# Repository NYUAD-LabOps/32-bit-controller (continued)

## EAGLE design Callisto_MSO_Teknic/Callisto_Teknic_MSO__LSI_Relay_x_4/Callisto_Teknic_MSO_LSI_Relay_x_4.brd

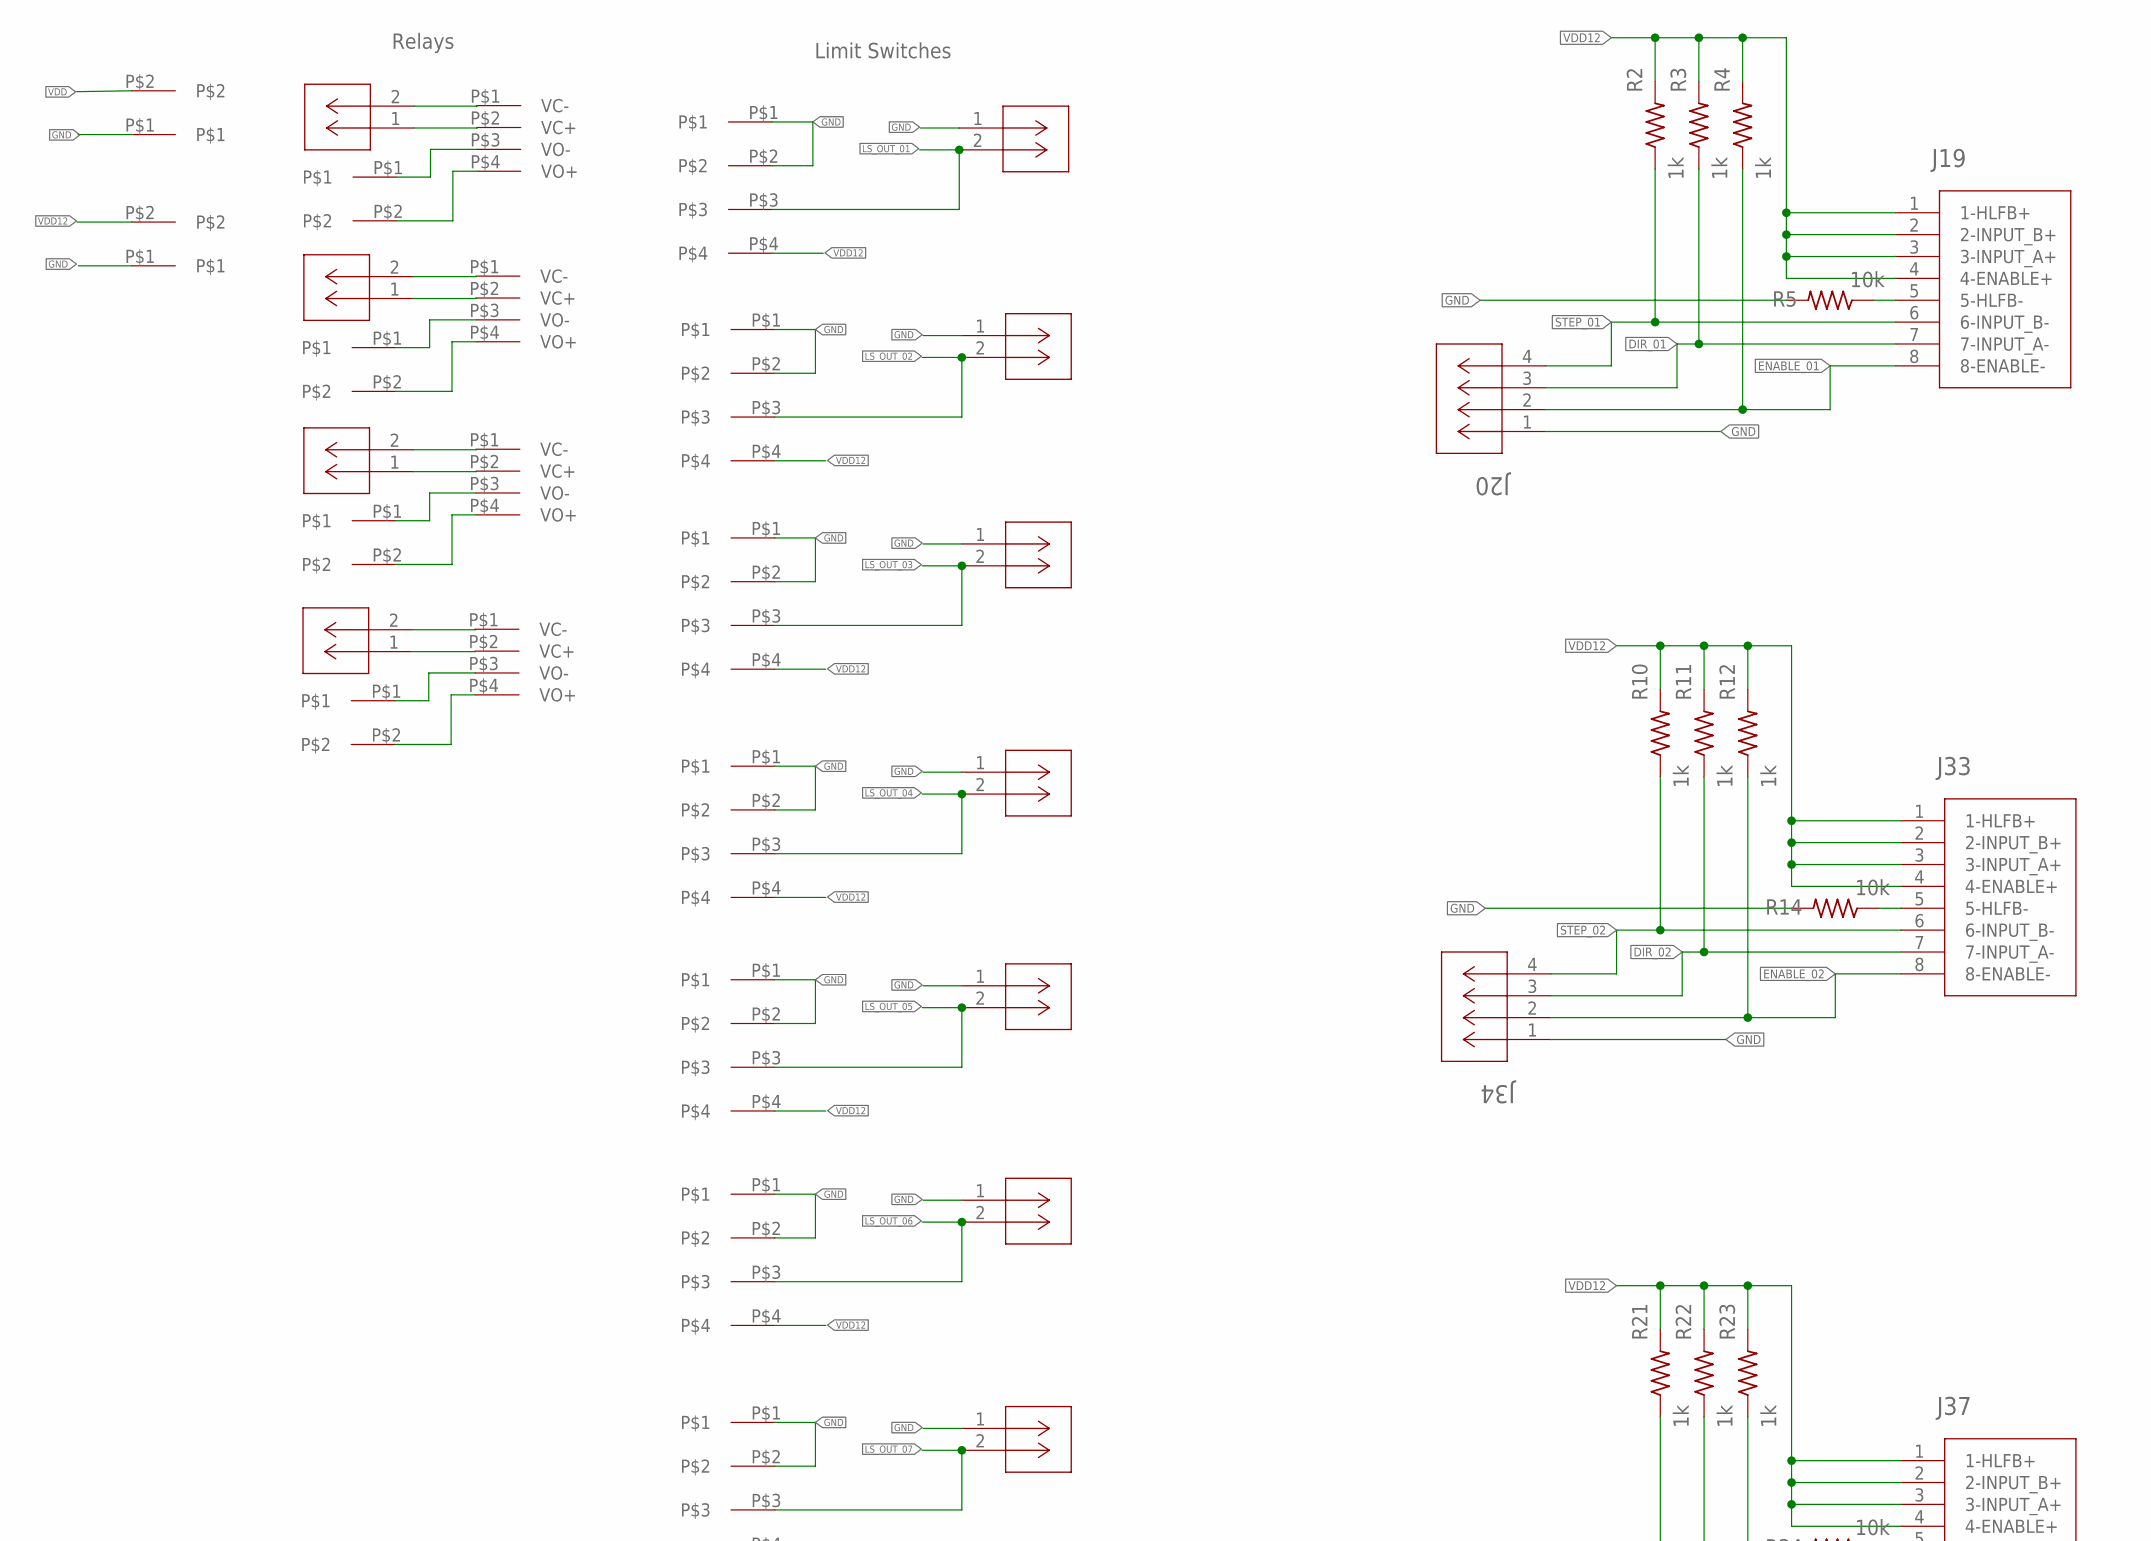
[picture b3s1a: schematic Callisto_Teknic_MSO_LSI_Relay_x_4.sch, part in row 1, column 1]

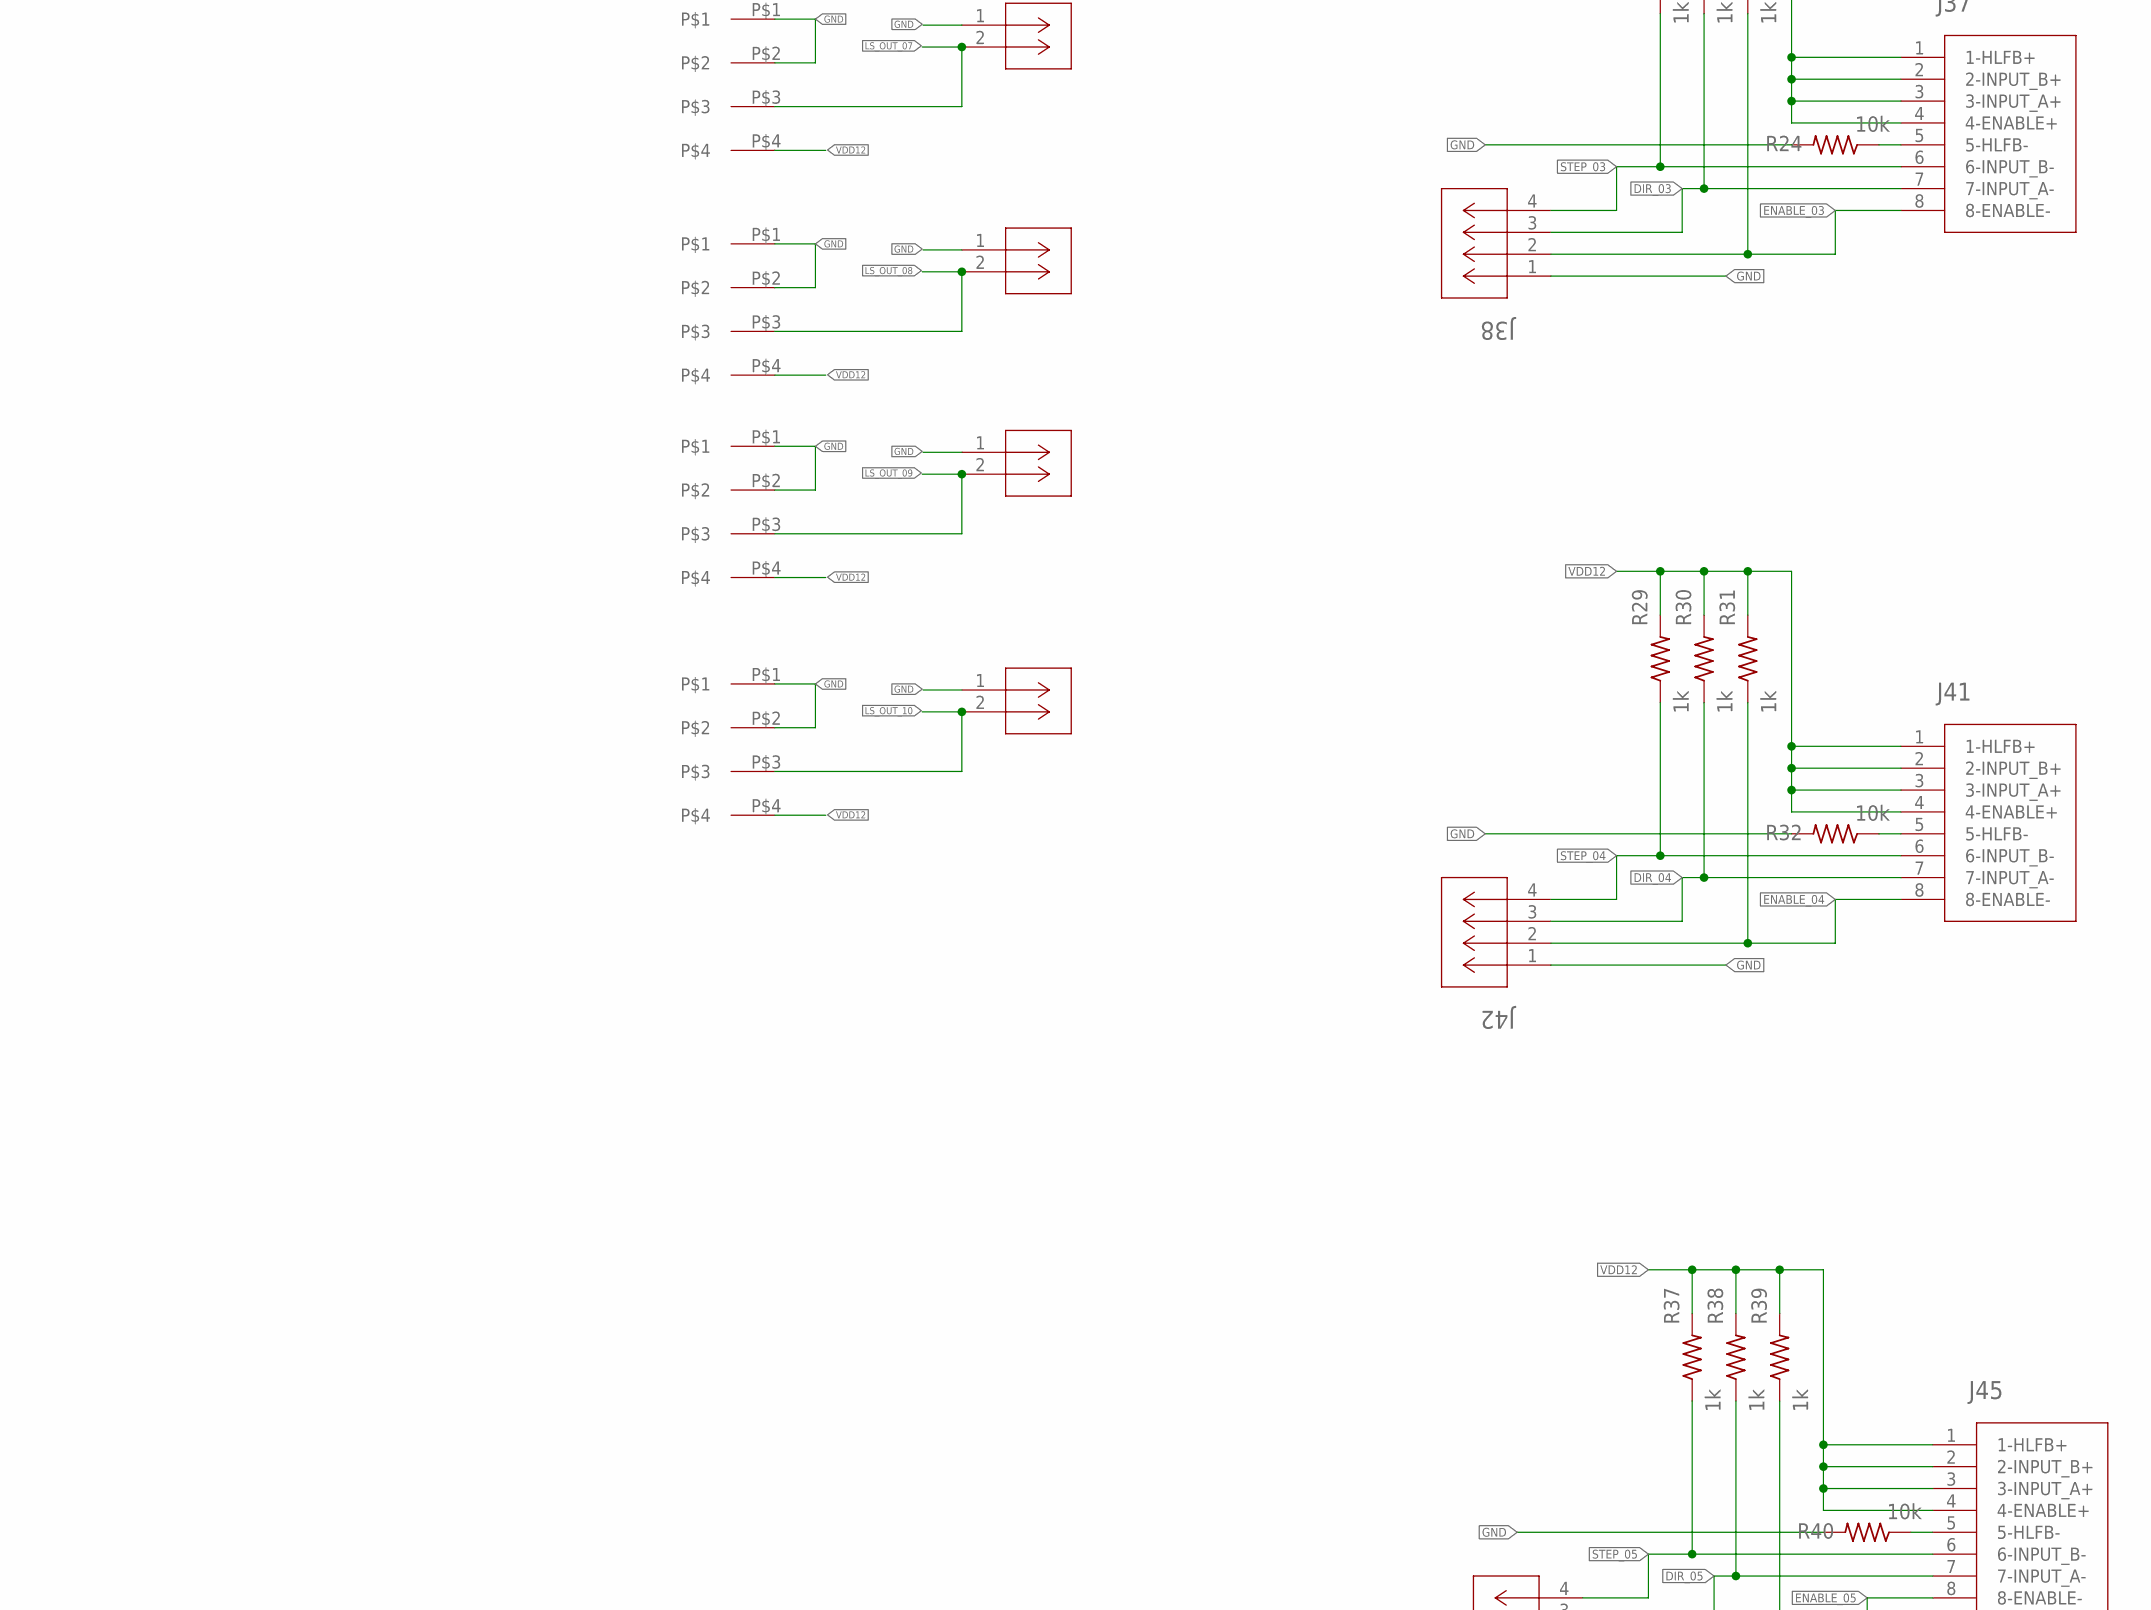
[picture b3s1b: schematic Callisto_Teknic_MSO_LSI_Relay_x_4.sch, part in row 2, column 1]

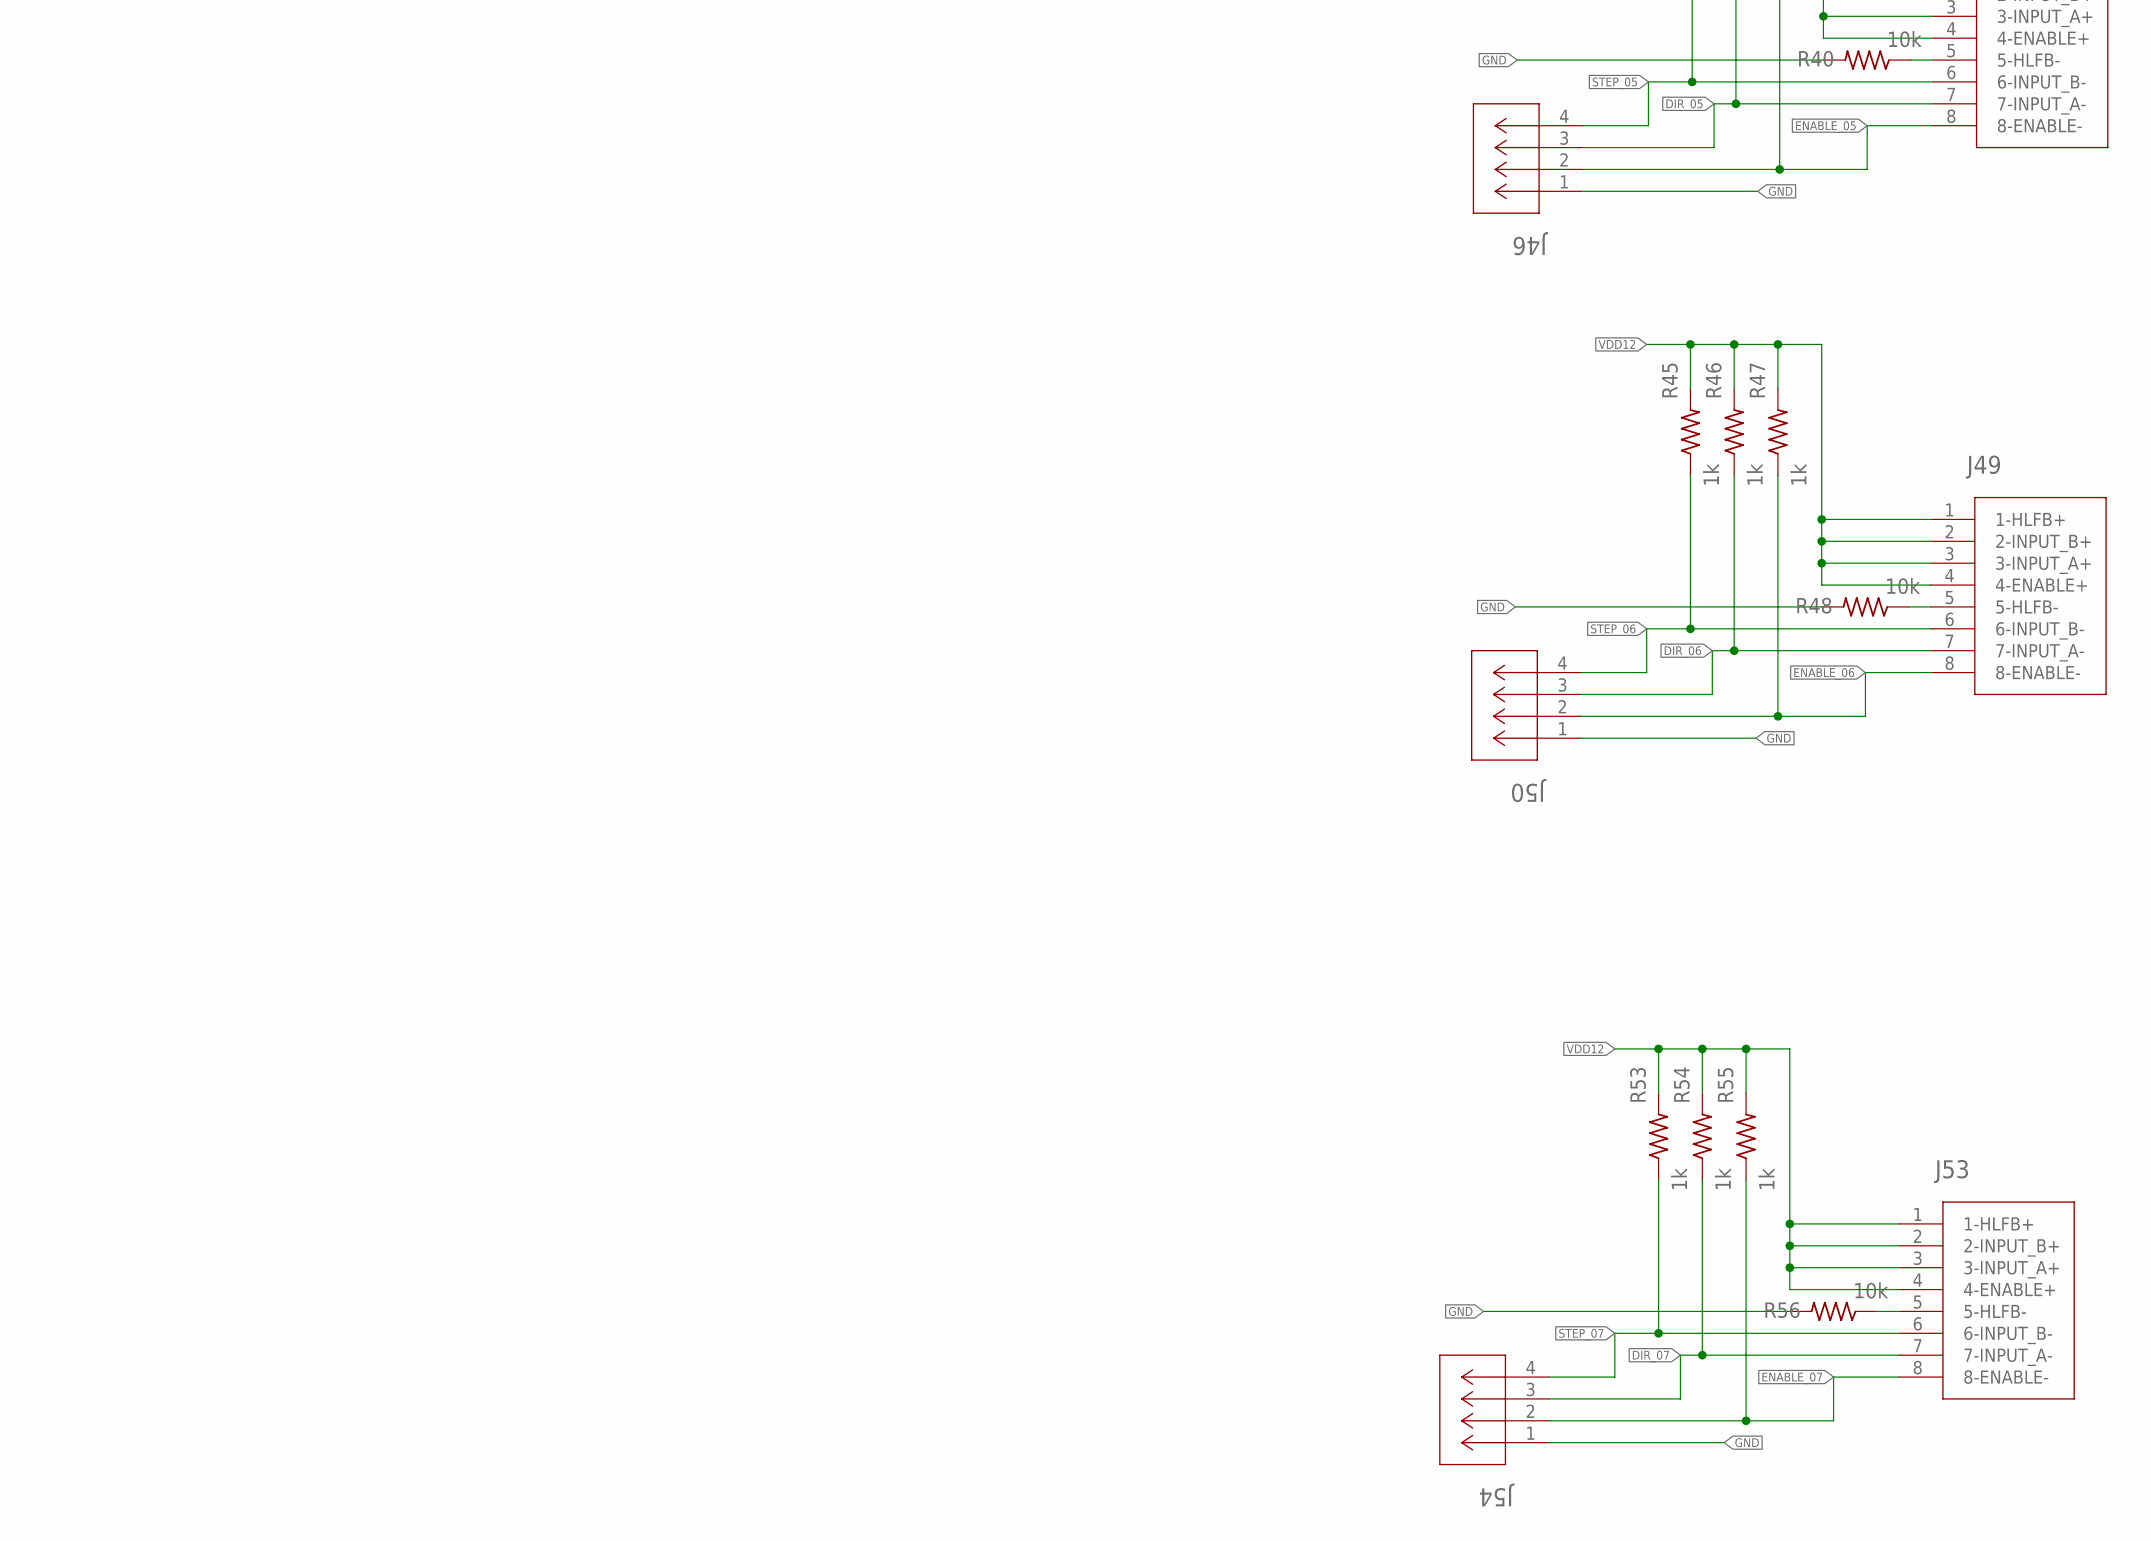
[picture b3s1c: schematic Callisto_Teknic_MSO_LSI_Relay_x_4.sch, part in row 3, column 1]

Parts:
J1, J2, J5, J7, J9, J11: 2-pos; 2_3.81MM_PITCH
J4, J6, J8, J10, J13, J15, J17, J21, J23, J25, J27, J29, J31, J39: CONN_530470210_PICOBLADE_X_2; CON_530470210_MOL
J14, J16, J18, J22, J24, J26, J28, J30, J32, J40: 4-pos; 1X4_3.81MM_PITCH
J19, J33, J37, J41, J45, J49, J53: TEKNIC_8PIN_MOTOR; CON_39281083
J20, J34, J38, J42, J46, J50, J54: CONN_530470410_PICOBLADE_X_4; CON_530470410_MOL
R2, R3, R4, R10, R11, R12, R21, R22, R23, R29, R30, R31, R37, R38, R39, R45, R46, R47, R53, R54, R55: 1k; 0805
R5, R14, R24, R32, R40, R48, R56: 10k; 0805
U$1, U$2, U$3, U$4: RELAY_KYOTO_KF0604D

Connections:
DIR_01: J19.7 (7-INPUT_A-), J20.3, R3.1
DIR_02: J33.7 (7-INPUT_A-), J34.3, R11.1
DIR_03: J37.7 (7-INPUT_A-), J38.3, R22.1
DIR_04: J41.7 (7-INPUT_A-), J42.3, R30.1
DIR_05: J45.7 (7-INPUT_A-), J46.3, R38.1
DIR_06: J49.7 (7-INPUT_A-), J50.3, R46.1
DIR_07: J53.7 (7-INPUT_A-), J54.3, R54.1
ENABLE_01: J19.8 (8-ENABLE-), J20.2, R4.1
ENABLE_02: J33.8 (8-ENABLE-), J34.2, R12.1
ENABLE_03: J37.8 (8-ENABLE-), J38.2, R23.1
ENABLE_04: J41.8 (8-ENABLE-), J42.2, R31.1
ENABLE_05: J45.8 (8-ENABLE-), J46.2, R39.1
ENABLE_06: J49.8 (8-ENABLE-), J50.2, R47.1
ENABLE_07: J53.8 (8-ENABLE-), J54.2, R55.1
GND: J1.P$1, J2.P$1, J13.1, J14.P$1, J14.P$2, J15.1, J16.P$1, J16.P$2, J17.1, J18.P$1, J18.P$2, J20.1, J21.1, J22.P$1, J22.P$2, J23.1, J24.P$1, J24.P$2, J25.1, J26.P$1, J26.P$2, J27.1, J28.P$1, J28.P$2, J29.1, J30.P$1, J30.P$2, J31.1, J32.P$1, J32.P$2, J34.1, J38.1, J39.1, J40.P$1, J40.P$2, J42.1, J46.1, J50.1, J54.1, R5.2, R14.2, R24.2, R32.2, R40.2, R48.2, R56.2
LS_OUT_01: J13.2, J14.P$3
LS_OUT_02: J17.2, J18.P$3
LS_OUT_03: J21.2, J22.P$3
LS_OUT_04: J25.2, J26.P$3
LS_OUT_05: J29.2, J30.P$3
LS_OUT_06: J15.2, J16.P$3
LS_OUT_07: J23.2, J24.P$3
LS_OUT_08: J27.2, J28.P$3
LS_OUT_09: J31.2, J32.P$3
LS_OUT_10: J39.2, J40.P$3
unnamed: J19.5 (5-HLFB-), R5.1
unnamed: J4.1, U$1.P$2 (VC+)
unnamed: J4.2, U$1.P$1 (VC-)
unnamed: J5.P$1, U$1.P$3 (VO-)
unnamed: J5.P$2, U$1.P$4 (VO+)
unnamed: J6.1, U$2.P$2 (VC+)
unnamed: J6.2, U$2.P$1 (VC-)
unnamed: J7.P$1, U$2.P$3 (VO-)
unnamed: J7.P$2, U$2.P$4 (VO+)
unnamed: J8.1, U$3.P$2 (VC+)
unnamed: J8.2, U$3.P$1 (VC-)
unnamed: J9.P$1, U$3.P$3 (VO-)
unnamed: J9.P$2, U$3.P$4 (VO+)
unnamed: J10.1, U$4.P$2 (VC+)
unnamed: J10.2, U$4.P$1 (VC-)
unnamed: J11.P$1, U$4.P$3 (VO-)
unnamed: J11.P$2, U$4.P$4 (VO+)
unnamed: J33.5 (5-HLFB-), R14.1
unnamed: J37.5 (5-HLFB-), R24.1
unnamed: J41.5 (5-HLFB-), R32.1
unnamed: J45.5 (5-HLFB-), R40.1
unnamed: J49.5 (5-HLFB-), R48.1
unnamed: J53.5 (5-HLFB-), R56.1
STEP_01: J19.6 (6-INPUT_B-), J20.4, R2.1
STEP_02: J33.6 (6-INPUT_B-), J34.4, R10.1
STEP_03: J37.6 (6-INPUT_B-), J38.4, R21.1
STEP_04: J41.6 (6-INPUT_B-), J42.4, R29.1
STEP_05: J45.6 (6-INPUT_B-), J46.4, R37.1
STEP_06: J49.6 (6-INPUT_B-), J50.4, R45.1
STEP_07: J53.6 (6-INPUT_B-), J54.4, R53.1
VDD: J1.P$2
VDD12: J2.P$2, J14.P$4, J16.P$4, J18.P$4, J19.1 (1-HLFB+), J19.2 (2-INPUT_B+), J19.3 (3-INPUT_A+), J19.4 (4-ENABLE+), J22.P$4, J24.P$4, J26.P$4, J28.P$4, J30.P$4, J32.P$4, J33.1 (1-HLFB+), J33.2 (2-INPUT_B+), J33.3 (3-INPUT_A+), J33.4 (4-ENABLE+), J37.1 (1-HLFB+), J37.2 (2-INPUT_B+), J37.3 (3-INPUT_A+), J37.4 (4-ENABLE+), J40.P$4, J41.1 (1-HLFB+), J41.2 (2-INPUT_B+), J41.3 (3-INPUT_A+), J41.4 (4-ENABLE+), J45.1 (1-HLFB+), J45.2 (2-INPUT_B+), J45.3 (3-INPUT_A+), J45.4 (4-ENABLE+), J49.1 (1-HLFB+), J49.2 (2-INPUT_B+), J49.3 (3-INPUT_A+), J49.4 (4-ENABLE+), J53.1 (1-HLFB+), J53.2 (2-INPUT_B+), J53.3 (3-INPUT_A+), J53.4 (4-ENABLE+), R2.2, R3.2, R4.2, R10.2, R11.2, R12.2, R21.2, R22.2, R23.2, R29.2, R30.2, R31.2, R37.2, R38.2, R39.2, R45.2, R46.2, R47.2, R53.2, R54.2, R55.2

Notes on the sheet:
Limit Switches
Relays

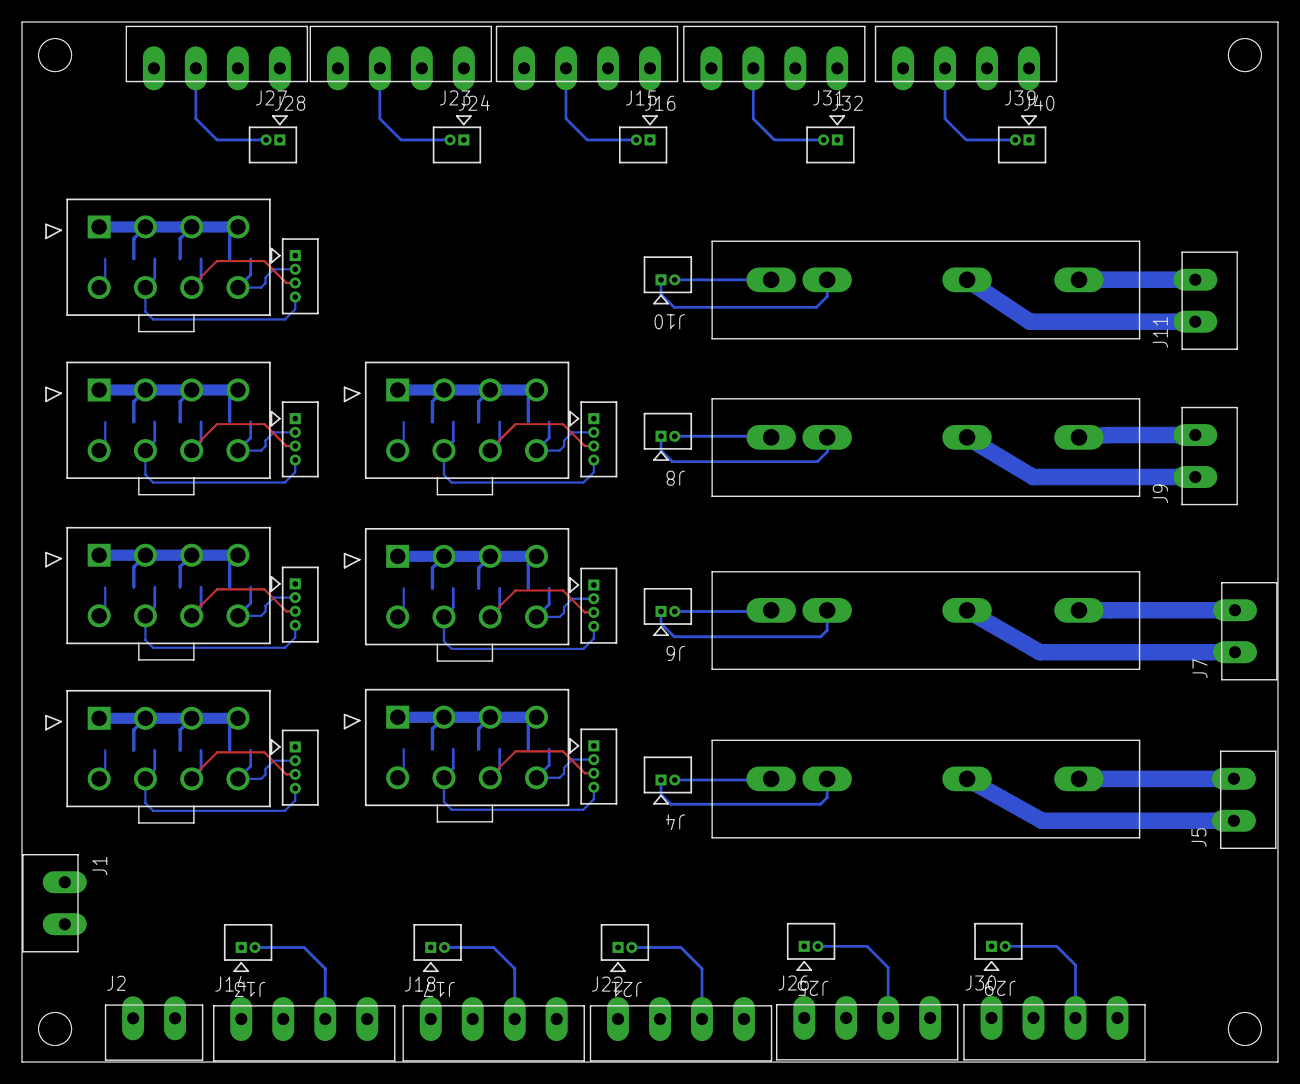
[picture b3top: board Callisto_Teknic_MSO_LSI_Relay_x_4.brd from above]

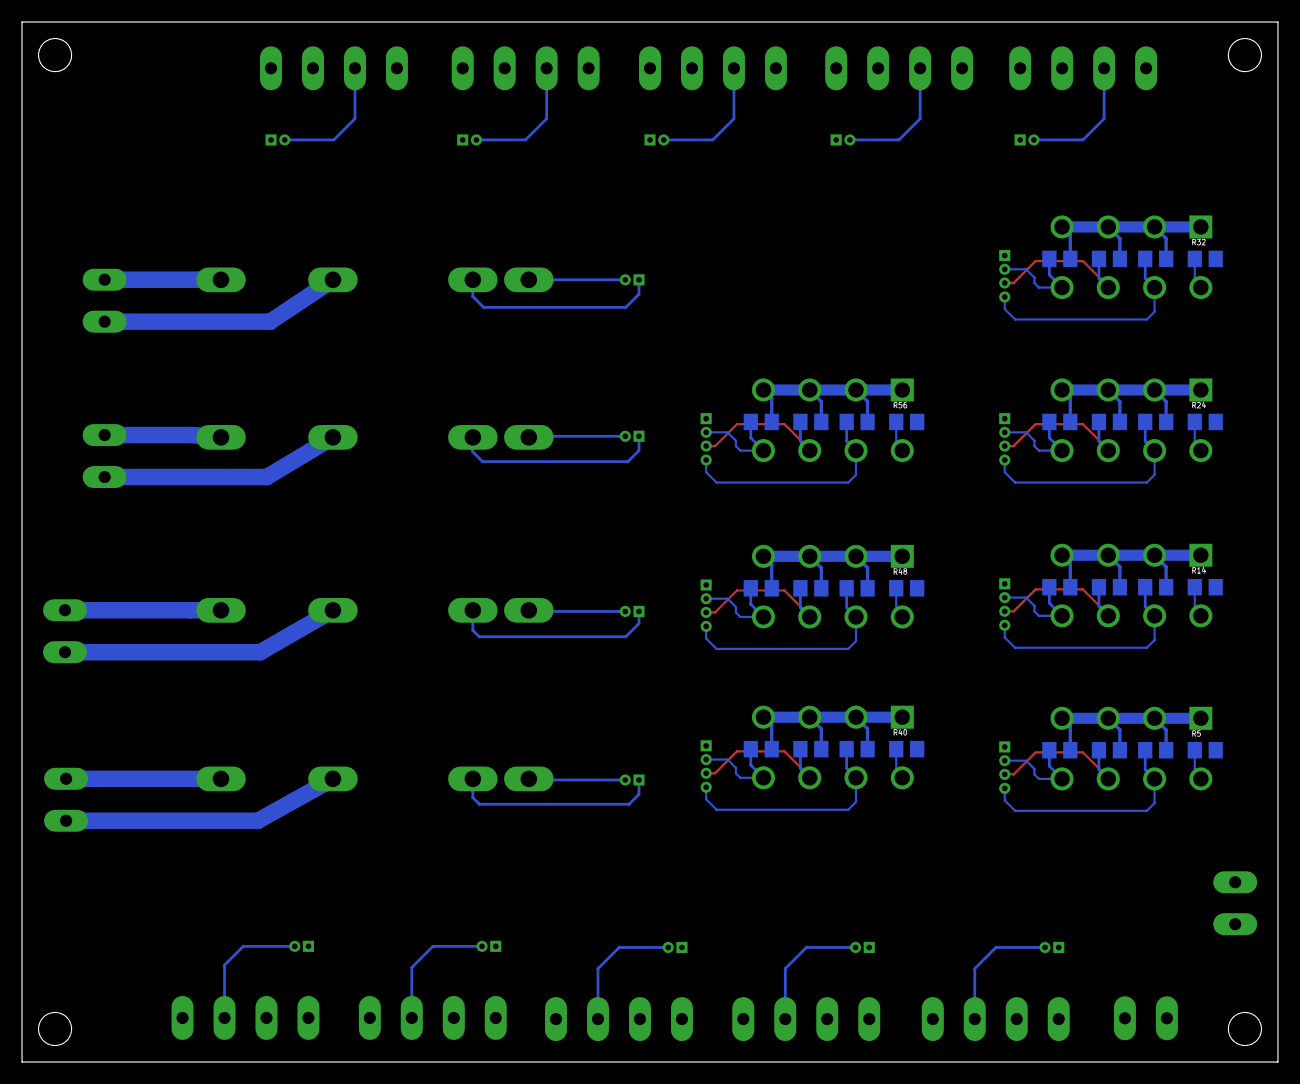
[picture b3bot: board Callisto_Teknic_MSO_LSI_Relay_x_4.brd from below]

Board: 2 copper layers, 114.0 x 94.4 mm, 76 parts (28 on the bottom side), 56 nets.

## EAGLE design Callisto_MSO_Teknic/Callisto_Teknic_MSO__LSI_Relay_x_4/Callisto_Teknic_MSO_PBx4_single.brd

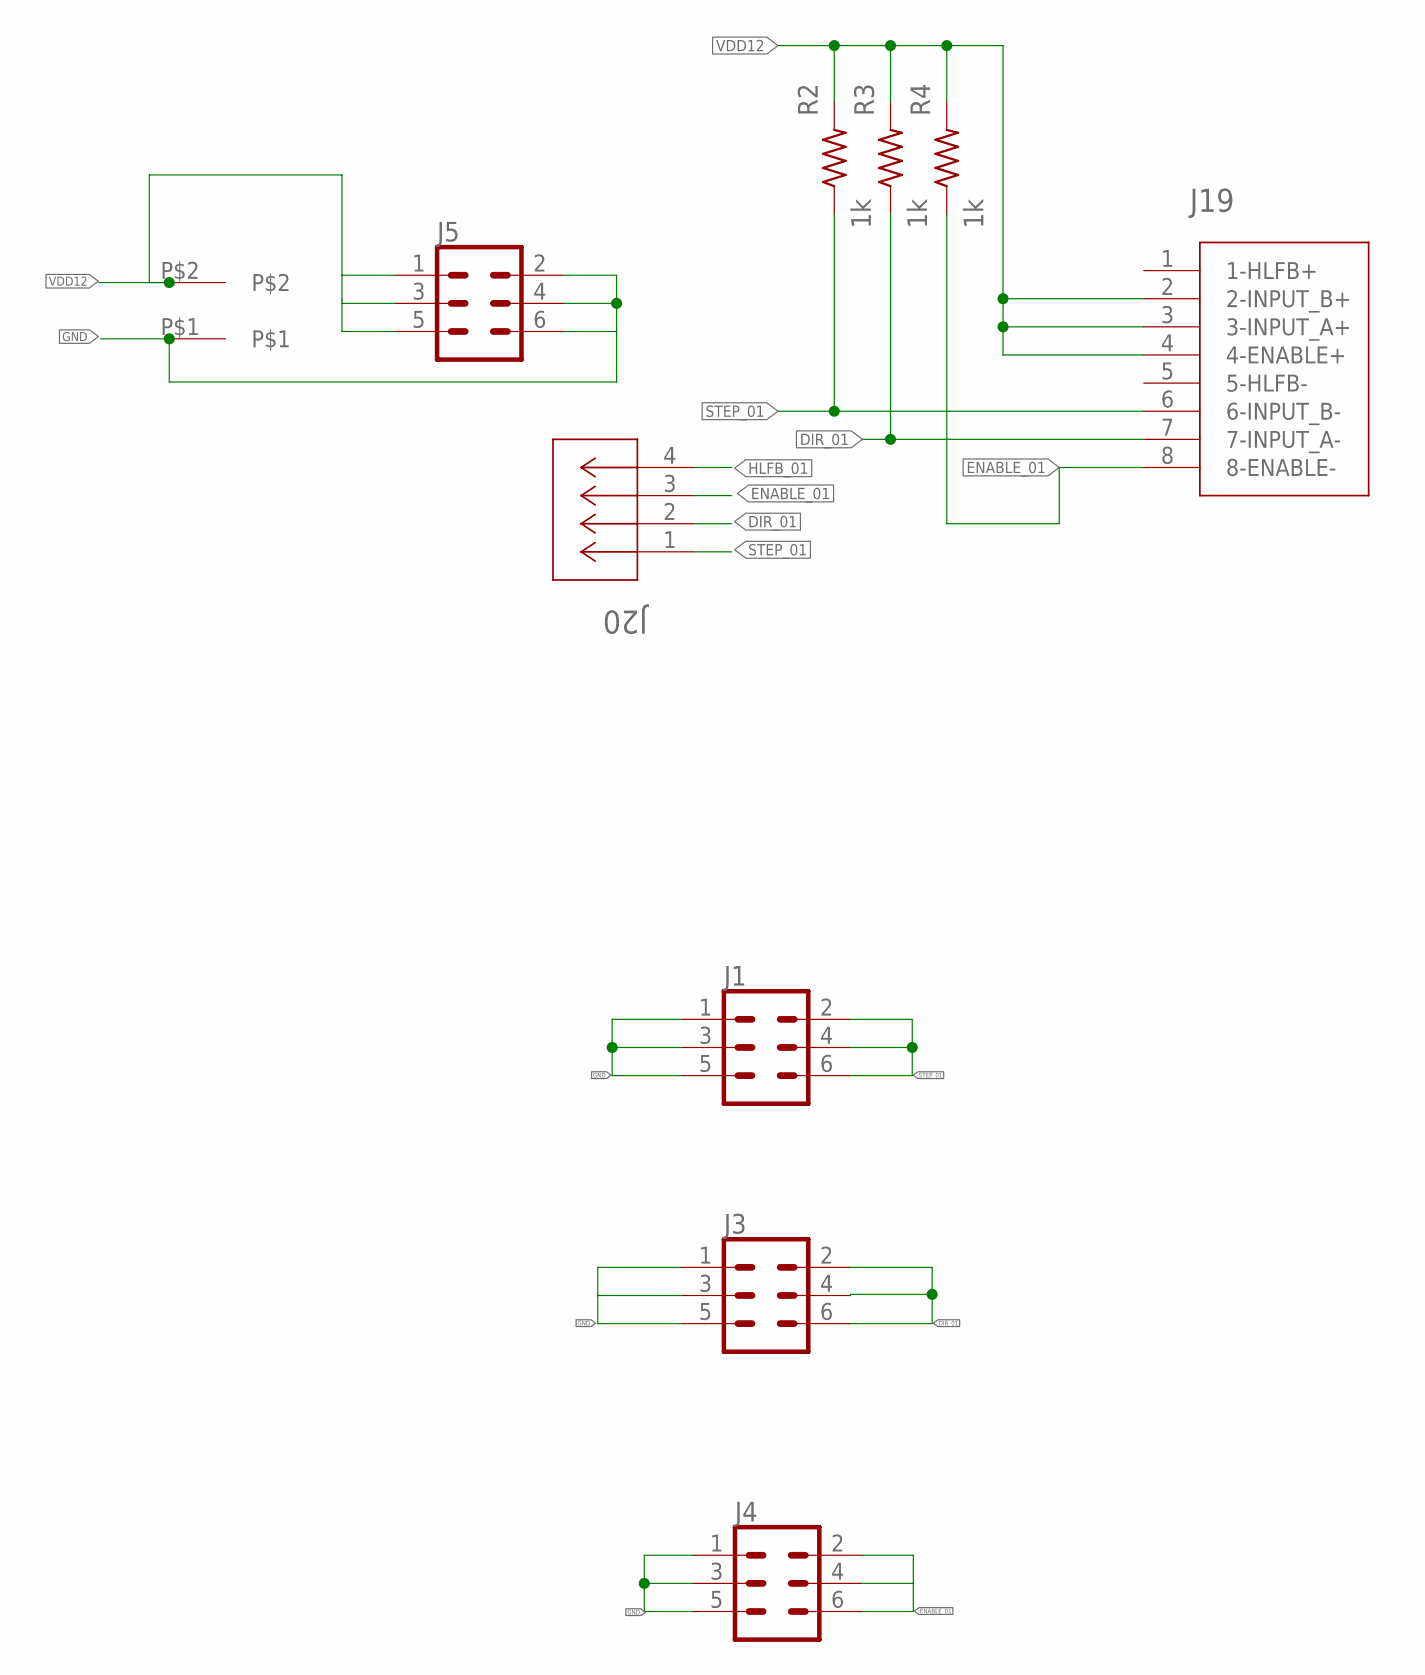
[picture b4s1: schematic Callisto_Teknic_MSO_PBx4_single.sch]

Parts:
J1, J3, J4, J5: CONN_03X2; 2X3
J2: 2-pos; 2_3.81MM_PITCH
J19: TEKNIC_8PIN_MOTOR; CON_39281083
J20: CONN_530470410_PICOBLADE_X_4; CON_530470410_MOL
R2, R3, R4: 1k; 0805

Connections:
DIR_01: J3.2, J3.4, J3.6, J19.7 (7-INPUT_A-), J20.2, R3.1
ENABLE_01: J4.2, J4.4, J4.6, J19.8 (8-ENABLE-), J20.3, R4.1
GND: J1.1, J1.3, J1.5, J2.P$1, J3.1, J3.3, J3.5, J4.1, J4.3, J4.5, J5.2, J5.4, J5.6
HLFB_01: J20.4
STEP_01: J1.2, J1.4, J1.6, J19.6 (6-INPUT_B-), J20.1, R2.1
VDD12: J2.P$2, J5.1, J5.3, J5.5, J19.2 (2-INPUT_B+), J19.3 (3-INPUT_A+), J19.4 (4-ENABLE+), R2.2, R3.2, R4.2

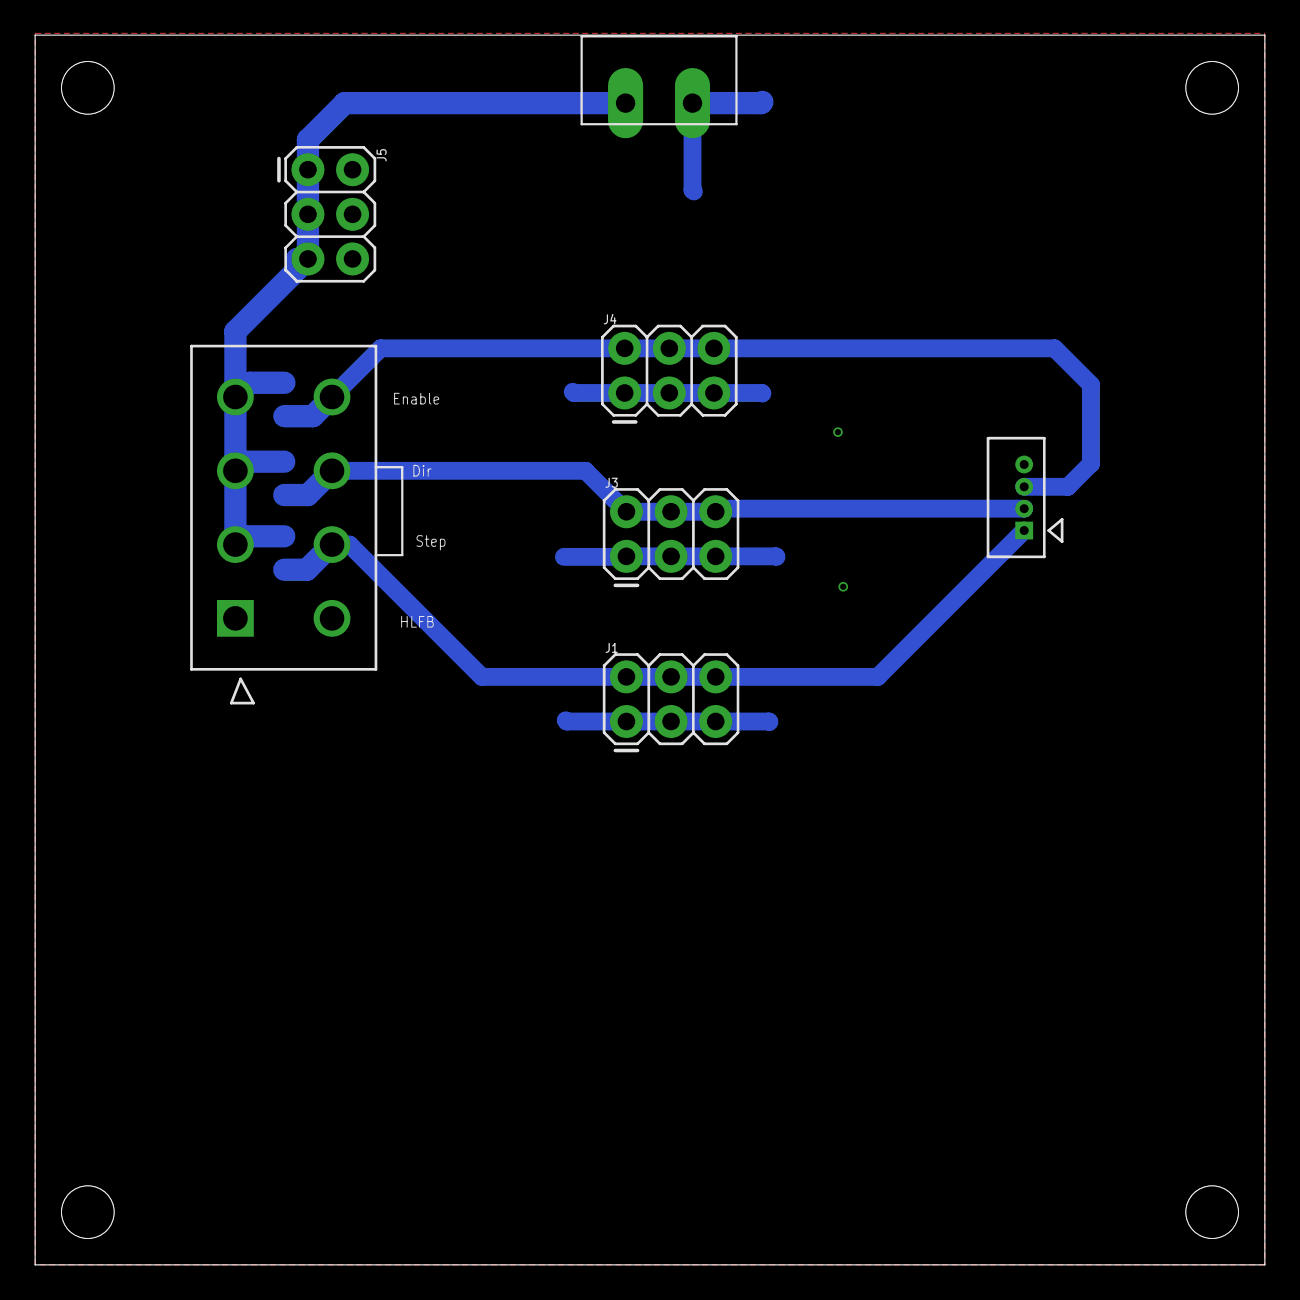
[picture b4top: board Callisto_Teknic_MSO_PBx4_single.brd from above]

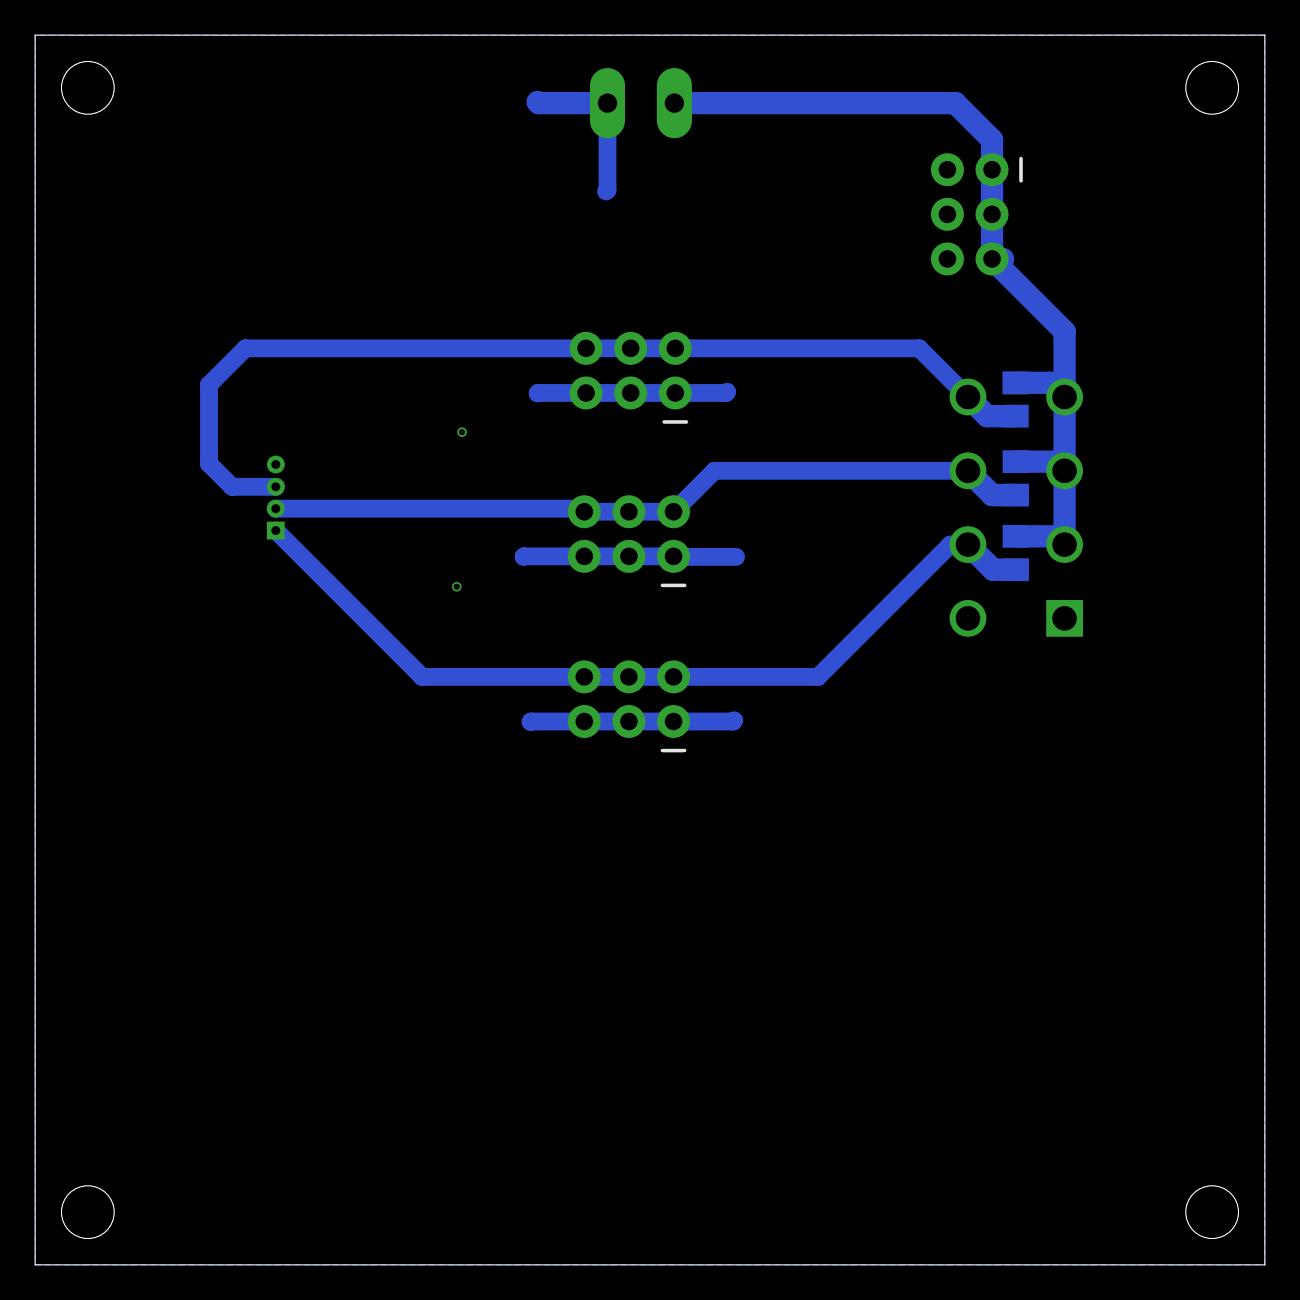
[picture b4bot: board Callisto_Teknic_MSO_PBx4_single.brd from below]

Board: 2 copper layers, 70.0 x 70.0 mm, 10 parts (3 on the bottom side), 5 nets.
